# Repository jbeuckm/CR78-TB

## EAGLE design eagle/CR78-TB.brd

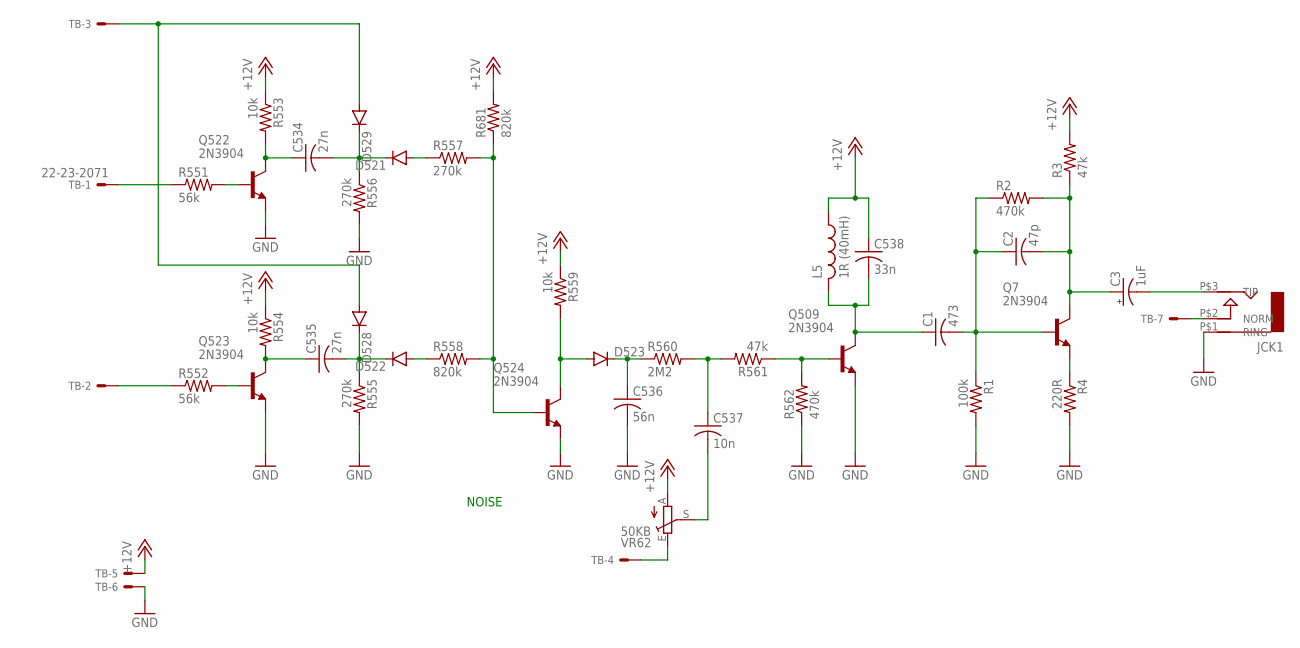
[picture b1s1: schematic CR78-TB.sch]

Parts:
C1: 473; C050-025X075
C2: 47p; C050-025X075
C3: 1uF; B45181A
C534, C535: 27n; C050-025X075
C536: 56n; C050-025X075
C537: 10n; C050-025X075
C538: 33n; C050-025X075
D521, D522, D523, D528, D529: DIODE1N4148; DIODE-1N4148
JCK1: AUDIO-JACK; ERTHENVAR-JACK-90DEG
L5: 1R (40mH); 0207/5V
Q7, Q509, Q522, Q523, Q524: 2N3904; TO92
R1: 100k; 0207/7
R2, R562: 470k; 0207/7
R3, R561: 47k; 0207/7
R4: 220R; 0207/7
R551, R552: 56k; 0207/5V
R553, R559: 10k; 0207/7
R554: 10k; 0207/10
R555, R556, R557: 270k; 0207/7
R558, R681: 820k; 0207/7
R560: 2M2; 0207/7
TB: 22-23-2071
VR62: 50KB; B64Y

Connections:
+12V: C538.1, L5.1, R3.2, R553.1, R554.1, R559.1, R681.2, TB.5, VR62.A
GND: C536.2, JCK1.P$1 (RING), Q509.3 (E), Q522.3 (E), Q523.3 (E), Q524.3 (E), R1.2, R4.2, R555.2, R556.2, R562.1, TB.6
unnamed: C535.2, D522.C, D528.C, R555.1
unnamed: D522.A, R558.1
unnamed: TB.4, VR62.E
unnamed: C536.1, D523.C, R560.1
unnamed: C537.1, R560.2, R561.2
unnamed: C1.1, C538.2, L5.2, Q509.1 (C)
unnamed: JCK1.P$2 (NORM), TB.7
unnamed: D523.A, Q524.1 (C), R559.2
unnamed: Q509.2 (B), R561.1, R562.2
unnamed: R552.1, TB.2
unnamed: Q524.2 (B), R557.2, R558.2, R681.1
unnamed: Q7.3 (E), R4.1
unnamed: C2.2, C3.+, Q7.1 (C), R2.2, R3.1
unnamed: C537.2, VR62.S
unnamed: C1.2, C2.1, Q7.2 (B), R1.1, R2.1
unnamed: C3.-, JCK1.P$3 (TIP)
unnamed: C534.1, Q522.1 (C), R553.2
unnamed: Q522.2 (B), R551.2
unnamed: C534.2, D521.C, D529.C, R556.1
unnamed: D521.A, R557.1
unnamed: R551.1, TB.1
unnamed: D528.A, D529.A, TB.3
unnamed: C535.1, Q523.1 (C), R554.2
unnamed: Q523.2 (B), R552.2

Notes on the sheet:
NOISE

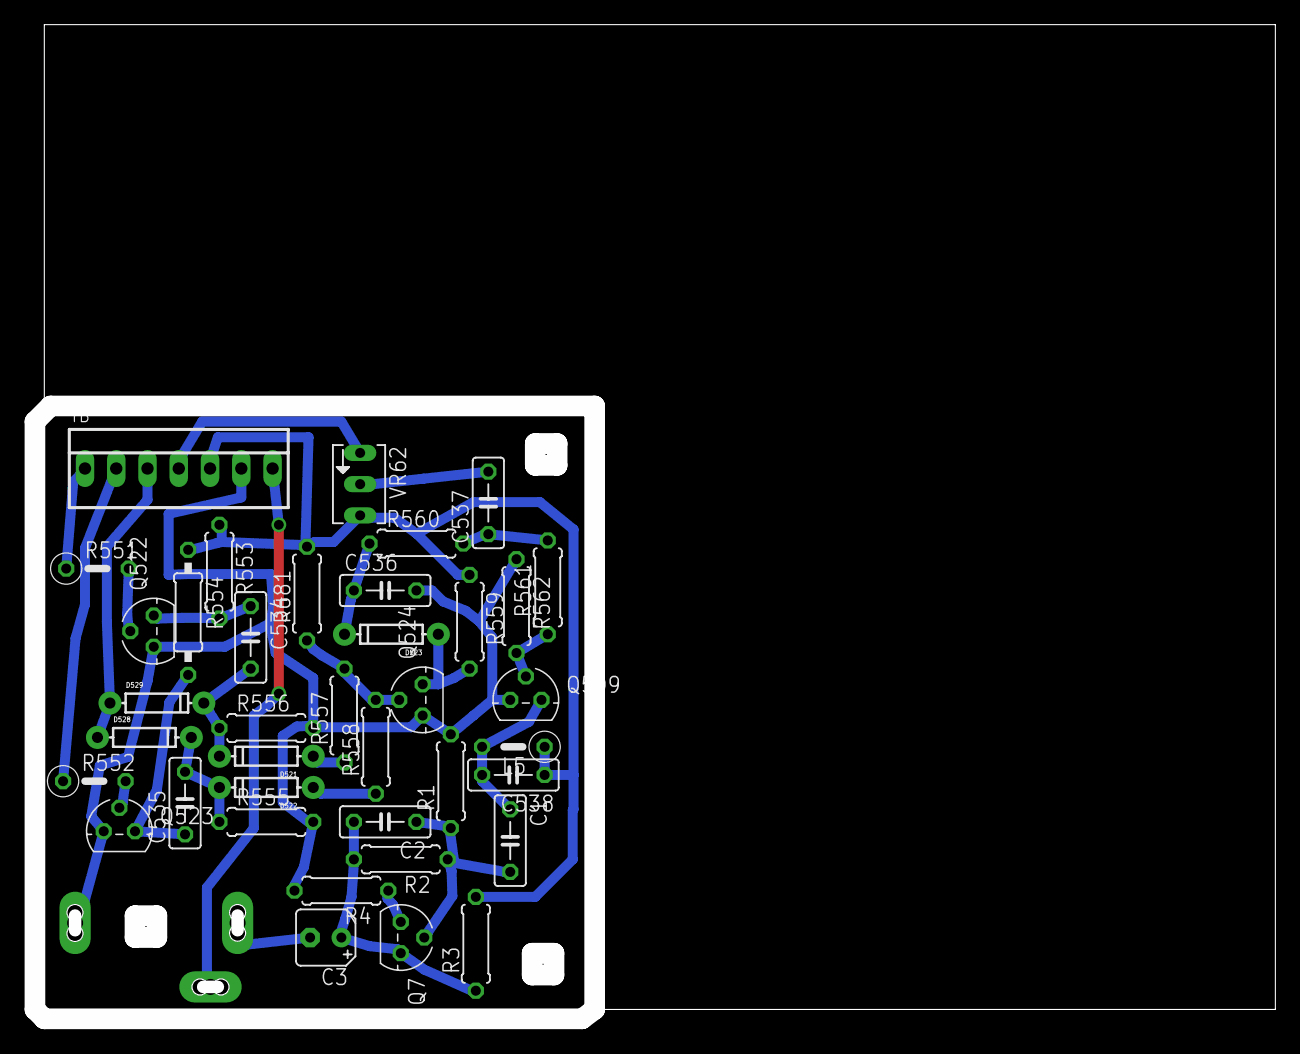
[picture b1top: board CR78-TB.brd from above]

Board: 2 copper layers, 100.8 x 80.8 mm, 39 parts (0 on the bottom side), 26 nets.

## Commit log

2016-06-14 rewrote power and ground
2016-06-14 killed loose ends

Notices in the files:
parts and their libraries:
SparkFun-DiscreteSemi: Licensing: Creative Commons ShareAlike 4.0 International - https://creativecommons.org/licenses/by-sa/4.0
